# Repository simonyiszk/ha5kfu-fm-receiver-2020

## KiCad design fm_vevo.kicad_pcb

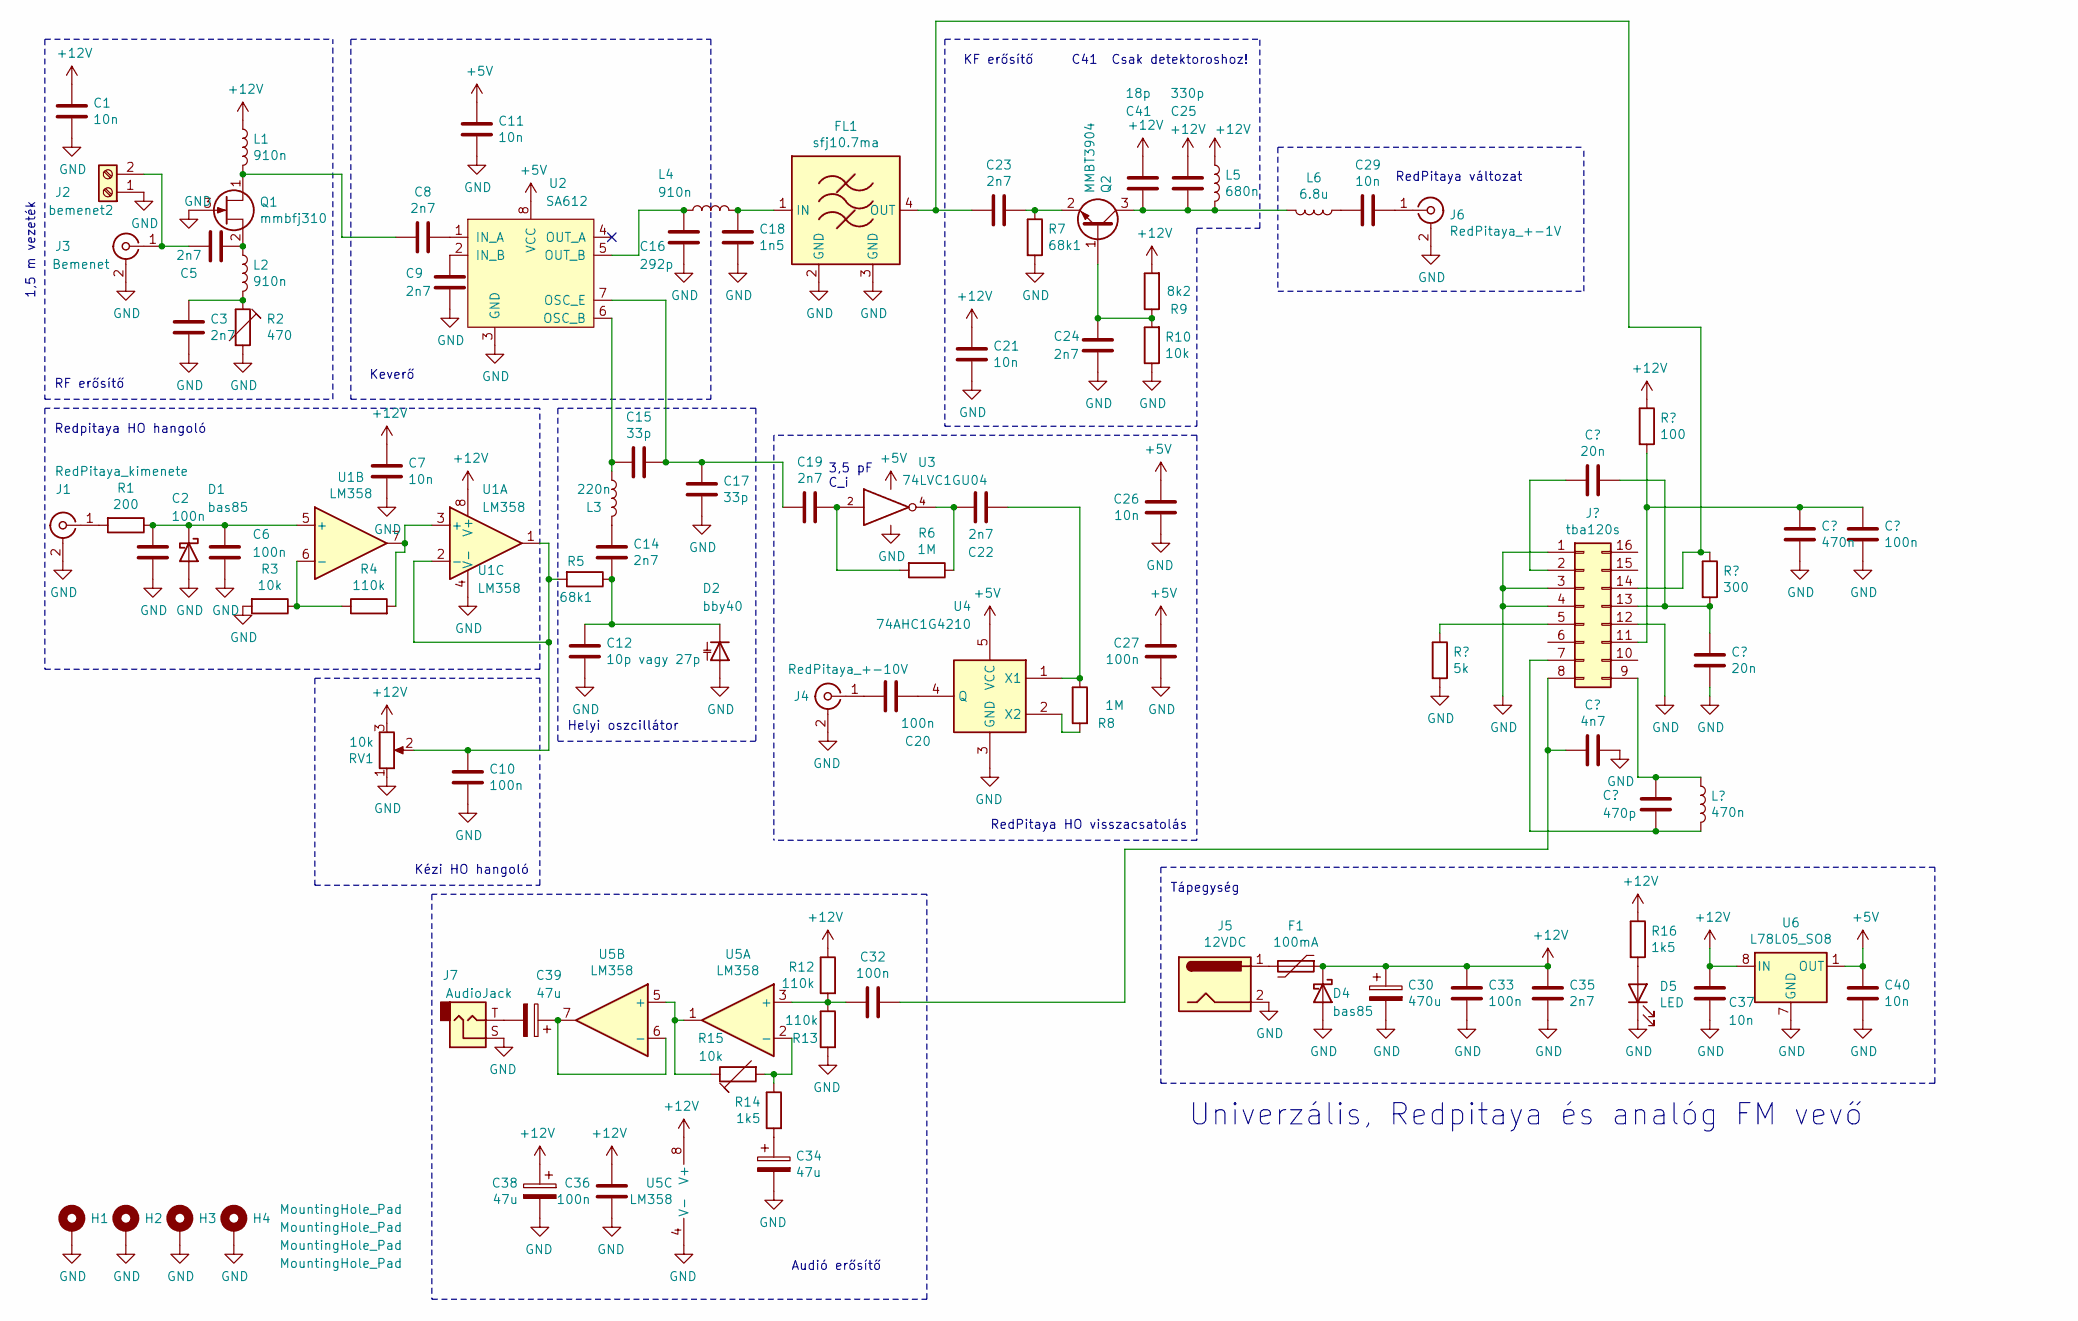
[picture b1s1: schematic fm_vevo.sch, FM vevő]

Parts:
C1, C7, C11, C21, C26, C29, C37, C40: 10n; C_0805_2012Metric_Pad1.15x1.40mm_HandSolder
C2, C6, C10, C20, C27, C32, C33, C36: 100n; C_0805_2012Metric_Pad1.15x1.40mm_HandSolder
C3, C5, C8, C9, C14, C19, C22, C23, C24, C35: 2n7; C_0805_2012Metric_Pad1.15x1.40mm_HandSolder
C12: 10p vagy 27p; C_0805_2012Metric_Pad1.15x1.40mm_HandSolder
C15, C17: 33p; C_0805_2012Metric_Pad1.15x1.40mm_HandSolder
C16: 292p; C_0805_2012Metric_Pad1.15x1.40mm_HandSolder
C18: 1n5; C_0805_2012Metric_Pad1.15x1.40mm_HandSolder
C25: 330p; C_0805_2012Metric_Pad1.15x1.40mm_HandSolder
C30: 470u; CP_Radial_D8.0mm_P3.50mm
C34, C38, C39: 47u; CP_Radial_D5.0mm_P2.00mm
C41: 18p; C_0805_2012Metric_Pad1.15x1.40mm_HandSolder
D1, D4: bas85; D_MiniMELF_Handsoldering
D2: bby40; D_SOT-23_ANK
D5: LED; LED_1206_3216Metric_Pad1.42x1.75mm_HandSolder
F1: 100mA; Fuse_1812_4532Metric_Pad1.30x3.40mm_HandSolder
FL1: sfj10.7ma
H1, H2, H3, H4: MountingHole_Pad; MountingHole_3mm_Pad
J1: RedPitaya_kimenete; SMA_Amphenol_132289_EdgeMount
J2: bemenet2; TerminalBlock_bornier-2_P5.08mm
J3: Bemenet; SMA_Amphenol_132289_EdgeMount
J4: RedPitaya_+-10V; SMA_Amphenol_132289_EdgeMount
J5: 12VDC; BarrelJack_Wuerth_6941xx301002
J6: RedPitaya_+-1V; SMA_Amphenol_132289_EdgeMount
J7: AudioJack; js35-09
L1, L2, L4: 910n; L_0805_2012Metric_Pad1.15x1.40mm_HandSolder
L3: 220n; L_0805_2012Metric_Pad1.15x1.40mm_HandSolder
L5: 680n; L_1210_3225Metric_Pad1.42x2.65mm_HandSolder
L6: 6.8u; L_1210_3225Metric_Pad1.42x2.65mm_HandSolder
Q1: mmbfj310; SOT-23_Handsoldering
Q2: MMBT3904; SOT-23_Handsoldering
R1: 200; R_0805_2012Metric_Pad1.15x1.40mm_HandSolder
R2: 470; Potentiometer_Piher_PT-15-V02_Vertical
R3, R10: 10k; R_0805_2012Metric_Pad1.15x1.40mm_HandSolder
R4, R12, R13: 110k; R_0805_2012Metric_Pad1.15x1.40mm_HandSolder
R5, R7: 68k1; R_0805_2012Metric_Pad1.15x1.40mm_HandSolder
R6, R8: 1M; R_0805_2012Metric_Pad1.15x1.40mm_HandSolder
R9: 8k2; R_0805_2012Metric_Pad1.15x1.40mm_HandSolder
R14, R16: 1k5; R_0805_2012Metric_Pad1.15x1.40mm_HandSolder
R15: 10k; Potentiometer_Piher_PT-15-V02_Vertical
RV1: 10k; Potentiometer_Piher_PT-15-V02_Vertical
U1, U5: LM358; SOIC-8_3.9x4.9mm_P1.27mm
U2: SA612; SO-8_3.9x4.9mm_P1.27mm
U3: 74LVC1GU04; SOT-353_SC-70-5_Handsoldering
U4: 74AHC1G4210; SOT-353_SC-70-5
U6: L78L05_SO8; SOIC-8_3.9x4.9mm_P1.27mm

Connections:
+5V: C11.1, C26.1, C27.2, C40.1, U2.8 (VCC), U3.5 (VCC), U4.5 (VCC), U6.1 (OUT)
+12V: C1.1, C7.1, C21.1, C25.1, C30.1, C33.1, C35.1, C36.1, C37.1, C38.1, C41.1, D4.1 (K), F1.1, L1.1, L5.1, R9.2, R12.1, R16.1, RV1.3, U1.8 (V+), U5.8 (V+), U6.8 (IN)
unnamed: C2.1, C6.1, D1.1 (K), R1.1, U1.5 (+)
unnamed: C3.1, L2.2, R2.1
unnamed: C5.1, L2.1, Q1.2 (S)
unnamed: C5.2, J2.2, J3.1 (In)
unnamed: C8.1, U2.1 (IN_A)
unnamed: C8.2, L1.2, Q1.1 (D)
unnamed: C9.2, U2.2 (IN_B)
unnamed: C10.1, R5.2, RV1.2, U1.1, U1.2 (-)
unnamed: C12.1, C14.2, D2.1 (K), R5.1
unnamed: C15.1, C17.1, C19.1, U2.7 (OSC_E)
unnamed: C16.1, L4.1, U2.5 (OUT_B)
unnamed: C18.1, FL1.1 (IN), L4.2
unnamed: C19.2, R6.2, U3.2
unnamed: C20.1, J4.1 (In)
unnamed: C20.2, U4.4 (Q)
unnamed: C22.1, R8.1, U4.1 (X1)
unnamed: C22.2, R6.1, U3.4
unnamed: C23.1, Q2.2 (E), R7.1
unnamed: C23.2, FL1.4 (OUT)
unnamed: C24.1, Q2.1 (B), R9.1, R10.2
unnamed 22: C25.2, C41.2, L5.2, L6.2, Q2.3 (C); also elsewhere on the board
unnamed 23: C32.2; also elsewhere on the board
unnamed: C29.1, J6.1 (In)
unnamed: C29.2, L6.1
unnamed: C32.1, R12.2, R13.1, U5.3 (+)
unnamed: C34.1, R14.2
unnamed: C39.1, U5.6 (-), U5.7
unnamed: C39.2, J7.T
unnamed: D5.2 (A), R16.2
unnamed: F1.2, J5.1
unnamed: J1.1 (In), R1.2
unnamed: R3.1, R4.1, U1.6 (-)
unnamed: R4.2, U1.3 (+), U1.7
unnamed: R8.2, U4.2 (X2)
unnamed: R14.1, R15.2, U5.2 (-)
unnamed: R15.1, U5.1, U5.5 (+)

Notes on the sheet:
RedPitaya változat
Audió erősítő
1,5 m vezeték
Keverő
RF erősítő
KF erősítő
Redpitaya HO hangoló
Kézi HO hangoló
RedPitaya HO visszacsatolás
Helyi oszcillátor
Univerzális, Redpitaya és analóg FM vevő
Tápegység
3,5 pF C_i
C41 Csak detektoroshoz!

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
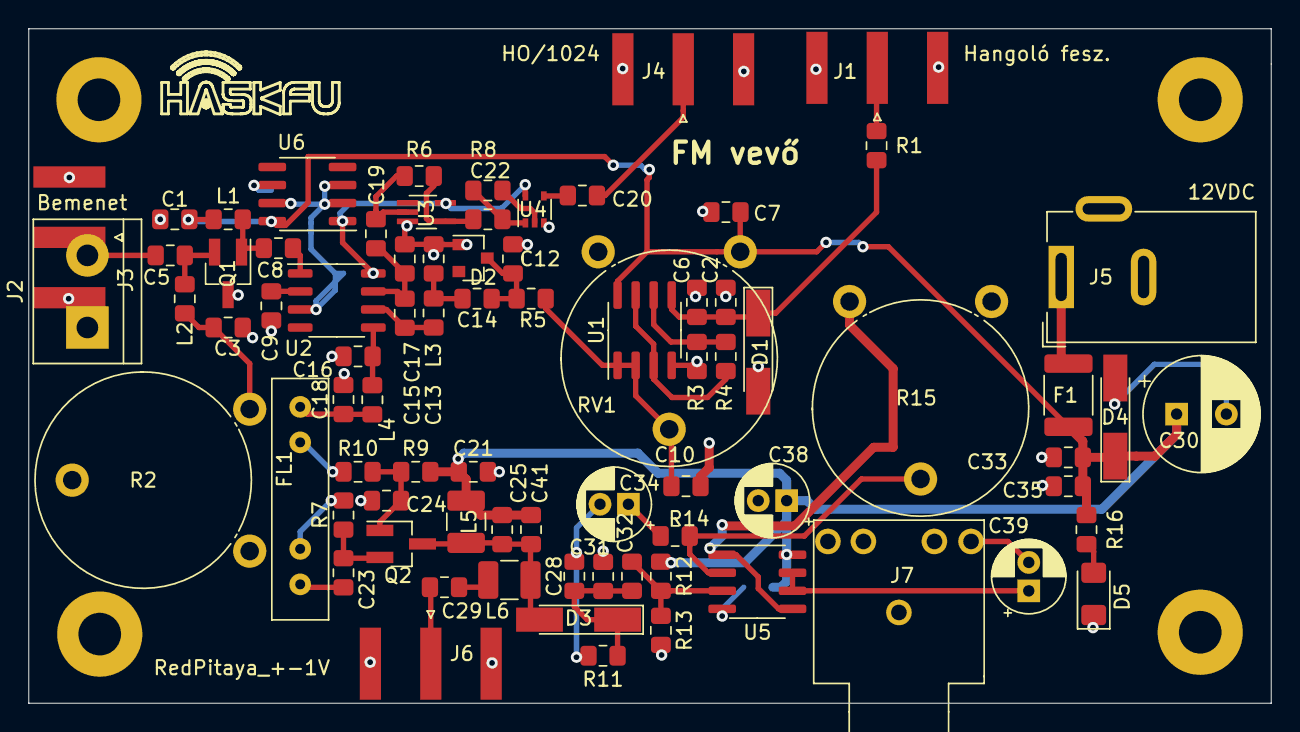
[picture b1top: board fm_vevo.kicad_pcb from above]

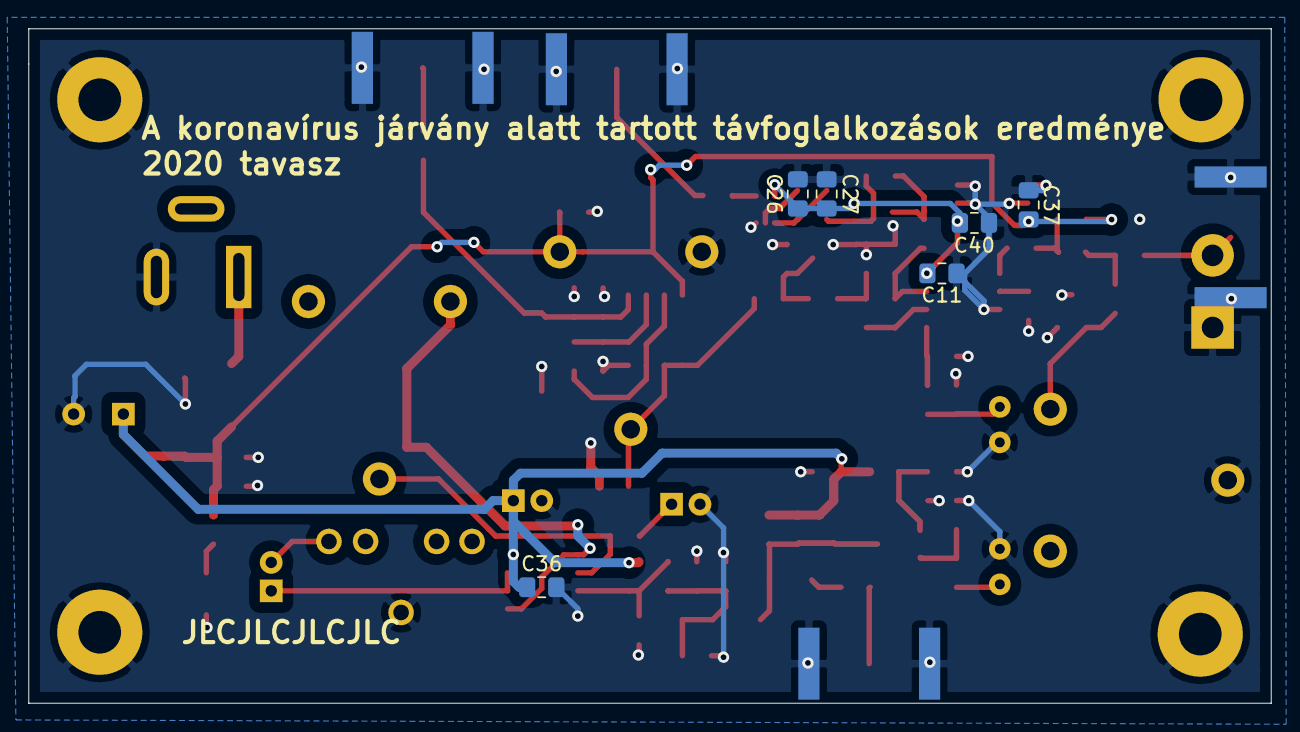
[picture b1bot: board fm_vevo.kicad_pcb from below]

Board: 2 copper layers, 87.5 x 47.5 mm, 89 parts (6 on the bottom side), 41 nets.

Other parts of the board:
C13, C28, C31: 2n7; C_0805_2012Metric_Pad1.15x1.40mm_HandSolder
D3: bas85; D_MiniMELF_Handsoldering
R11: 1k5; R_0805_2012Metric_Pad1.15x1.40mm_HandSolder

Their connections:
unnamed 22: D3.2; also elsewhere on the board
unnamed 23: C28.1, C31.1, D3.1, R11.1; also elsewhere on the board

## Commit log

2020-05-15 First version
2020-05-21 first sa612
2020-05-22 V1.2 Bement discordra és levlistára is
2020-05-24 Footprints nearly assosiated
2020-05-24 PCB v0.9
2020-05-29 Silkscreen
2020-06-03 Silk
2020-07-12 TBA120S demodulator added
